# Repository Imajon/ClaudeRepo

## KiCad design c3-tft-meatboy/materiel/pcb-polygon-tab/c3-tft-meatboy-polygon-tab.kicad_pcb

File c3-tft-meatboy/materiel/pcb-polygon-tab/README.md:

# c3-tft-meatboy — PCB « MA CONSOLE » (contour = textePCB.svg), routé

Géométrie identique à `../polygon-tab-lettres.svg`. Contour 110 x ~78 mm : lettres « MA CONSOLE » en haut, corps polygone.
Généré par `../make_kicad_tab.py` (+ routeur `../route_tab.py`), Gerbers exportés avec kicad-cli.

## Câblage (= .ino / ../montage-c3-tft.svg)
| Signal | GPIO C3 | Écran J3 / bouton |
|---|---|---|
| SCLK | 4 | SCL (broche 3) |
| MOSI | 6 | SDA (4) |
| CS | 7 | CS (7) |
| DC | 5 | DC (6) |
| RST | 10 | RES (5) |
| 3V3 | 3V3 | VCC (2) + BLK (8) |
| GND | GND | GND (1) + boutons |
| GAUCHE | 2 | SW1 (bouton le plus à gauche) |
| DROITE | 1 | SW2 |
| SAUT | 3 | SW3 (12x12) |
| IO21 / IO20 | 21 / 20 | pastilles de fil à gauche |
| IO0 / IO8 | 0 / 8 | pastilles de fil à droite |
GPIO9 (BOOT) et 5V ne sont pas utilisés.

## État
- **Routé** : 118 segments, 16 vias, 2 couches. **DRC : 0 violation, 0 non connecté** (`drc.rpt`).
- Cuivre des lettres (blanc du SVG) à 0,35 mm du bord ; règle cuivre/bord du projet = 0,25 mm (JLCPCB min 0,2).
- QR code cuivre 14 mm → https://brique.tierslieulecercle.fr.

## À vérifier avant de commander
- Le SuperMini est posé au dos, **vu de devant sa rangée GPIO0…5V est à DROITE** (x=64,12), USB-C vers le bas. Vérifie sur ta carte réelle : pastilles 2,4 x 1,3 mm, entraxe des rangées 15,24 mm.
- Boutons 6x6 / 12x12 : empreintes simplifiées (pastilles Ø1,8 / Ø2,2) ; pattes d'un même côté reliées dans le bouton.
- Le routeur est maison (grille 0,2 mm) : relire le tracé dans KiCad avant fabrication.

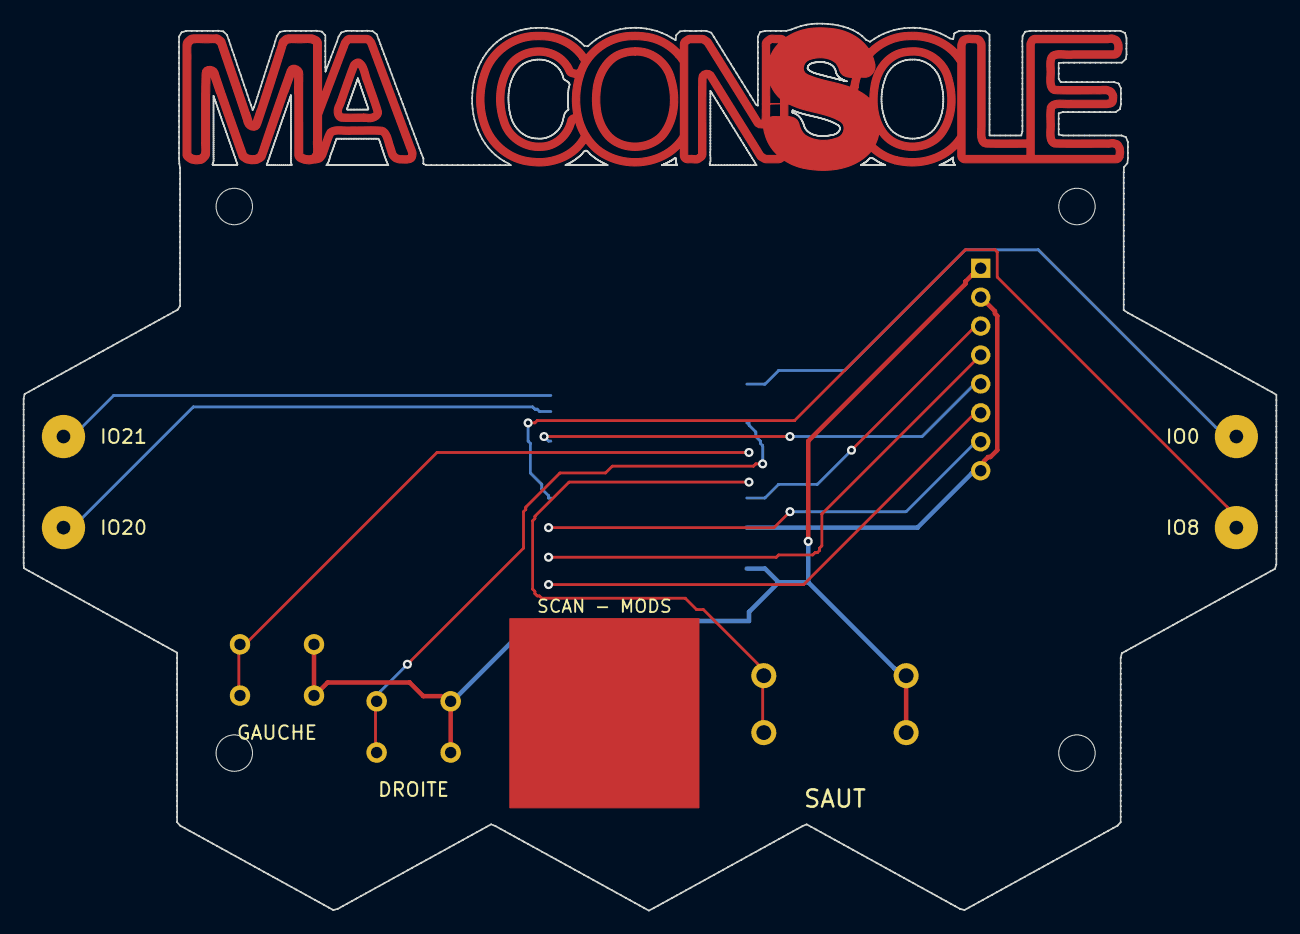
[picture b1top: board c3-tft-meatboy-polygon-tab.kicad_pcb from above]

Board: 2 copper layers, 110.0 x 77.9 mm, 13 parts (1 on the bottom side), 14 nets.

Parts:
J3: TFT_2.0in_header_1x08
MTG1, MTG2, MTG3, MTG4: MountingHole_3.2mm_M3
P1, P2, P3, P4: WirePad_3.8mm
SW1, SW2: SW_6x6
SW3: SW_12x12
U1: ESP32-C3_SuperMini_SMD

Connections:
+3V3: J3.2, J3.8, U1.6
CS: J3.7, U1.14
DC: J3.6, U1.16
DROITE: SW2.1, SW2.2, U1.2
GAUCHE: SW1.1, SW1.2, U1.3
GND: J3.1, SW1.3, SW1.4, SW2.3, SW2.4, SW3.3, SW3.4, U1.7
IO0: P3.1, U1.1
IO8: P4.1, U1.13
IO20: P2.1, U1.10
IO21: P1.1, U1.9
MOSI: J3.4, U1.15
RST: J3.5, U1.11
SAUT: SW3.1, SW3.2, U1.4
SCLK: J3.3, U1.5

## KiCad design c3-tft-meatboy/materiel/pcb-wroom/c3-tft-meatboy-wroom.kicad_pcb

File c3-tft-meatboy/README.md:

# Brique — la console de jeu que les enfants soudent eux-mêmes

**Brique** est une petite console de jeu portable à base d'**ESP32-C3** et d'un **écran TFT 2"**, conçue pour des ateliers avec des enfants (CM1 → 4ᵉ). Chaque enfant monte et soude sa propre console, puis joue à **Pixel Run**, un jeu de plateforme écrit pour la console.

Prochaine étape : laisser les enfants **créer leurs propres niveaux et règles avec une IA**, depuis un navigateur, sans rien installer.

---

## Le concept

Trois composants, trois boutons, un fer à souder. L'objectif : un objet simple à assembler, mais qui donne un vrai jeu fluide une fois allumé.

## Le matériel

| Composant | Rôle |
|---|---|
| ESP32-C3 Super Mini | Microcontrôleur Wi-Fi / ESP-NOW, USB-C |
| Écran TFT 2" ST7789 (SPI, 320×240) | Affichage |
| 3 boutons-poussoirs | Gauche (GPIO2), Droite (GPIO1), Saut (GPIO3) |
| Plaque à pastilles ou PCB hexagonal | Support |

## L'atelier

Les enfants partent des composants en vrac et repartent avec une console qui marche.

## Version 1 — prototype sur plaque à pastilles

Câblage fil à fil au dos, écran et boutons en façade.

## Version 2 — PCB hexagonal

Un PCB dédié en forme de briques hexagonales : moins de fils, montage plus rapide en atelier.

Fichiers KiCad et SVG du boîtier : [`materiel/`](materiel/).

## Le jeu : Pixel Run

- **100 niveaux** variés (ressorts, pics, blocs tombants, ennemis, scies…), étoiles à collecter, drapeau final.
- **Mode 2 joueurs** sans fil (ESP-NOW) : course avec le fantôme de l'adversaire.
- **Mini-jeux** bonus toutes les 10 étapes : Pong, Casse-brique, Invaders.
- **Quiz CM2** (maths, français, anglais) entre les niveaux, avec récompenses visuelles.
- **Classement partagé** entre consoles, boutique de skins, mascotte animée.
- Progression sauvegardée en mémoire flash.

## Compiler et flasher

Sketch Arduino : [`c3-tft-meatboy.ino`](c3-tft-meatboy.ino) (carte ESP32C3 Dev Module).

```bat
compiler-upload-c3-tft-meatboy.bat
```

Détails techniques et historique des versions : [`CONTEXTE.md`](CONTEXTE.md).

## La suite : créer son jeu avec l'IA

Idée : un firmware fixe (moteur, affichage, sons) et une IA qui génère uniquement **les niveaux et les règles** sous forme de données, envoyées à la console en quelques millisecondes depuis une page web. Le but n'est pas d'apprendre la syntaxe, mais de montrer aux enfants qu'ils peuvent **décrire, tester et corriger** un jeu qu'ils ont imaginé.

---

*AntiFaktory — 2026*

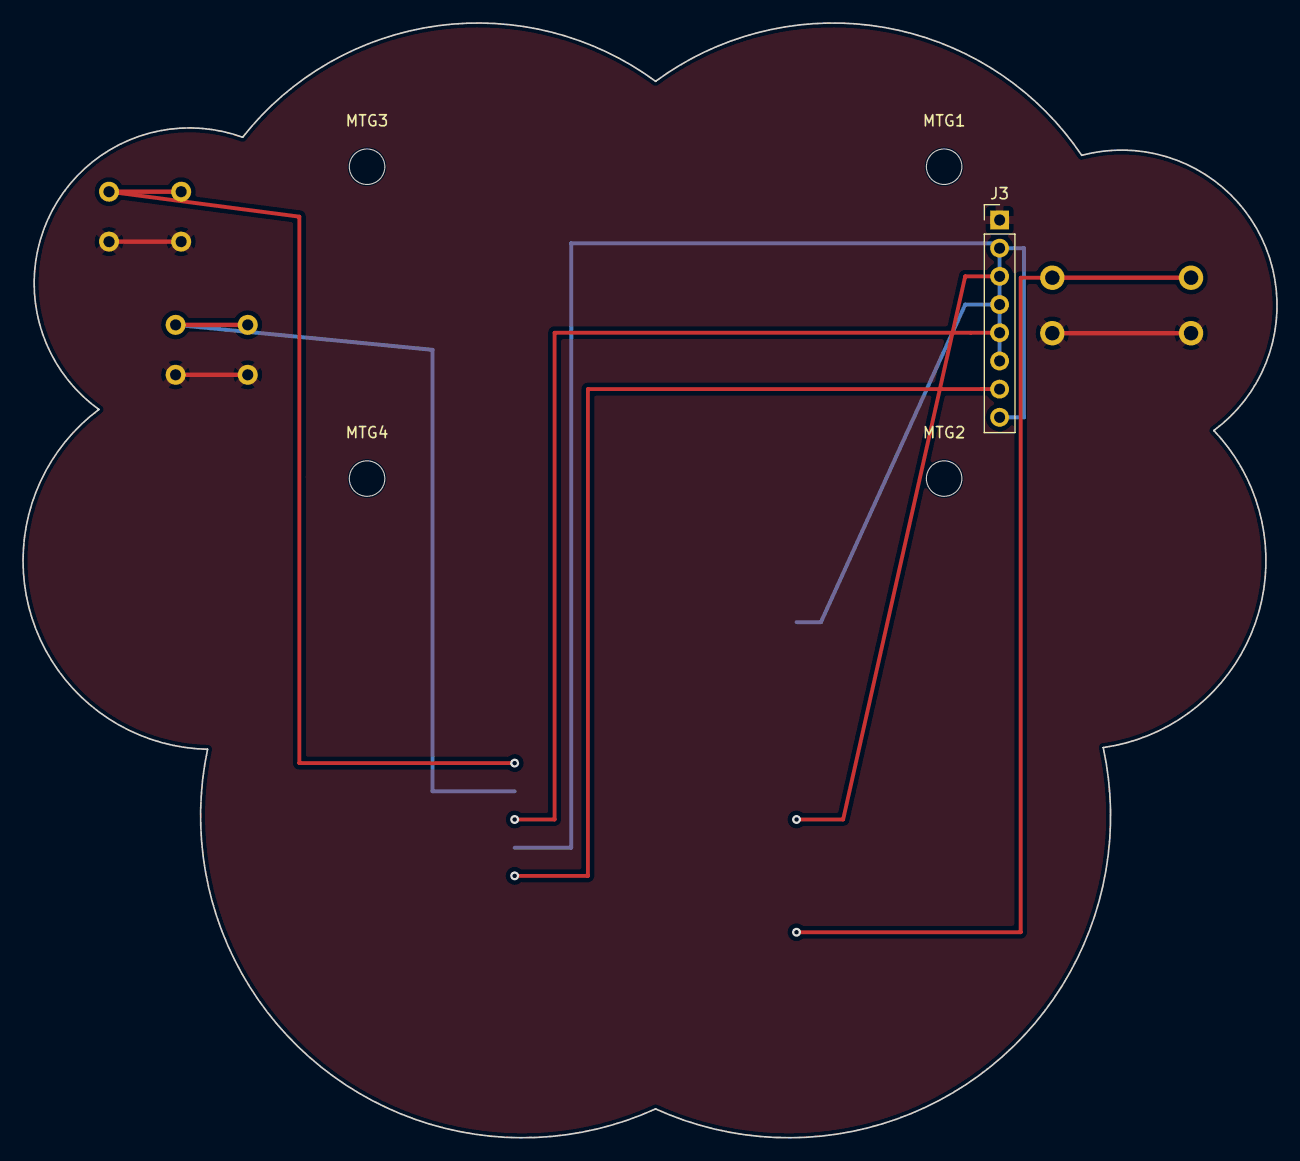
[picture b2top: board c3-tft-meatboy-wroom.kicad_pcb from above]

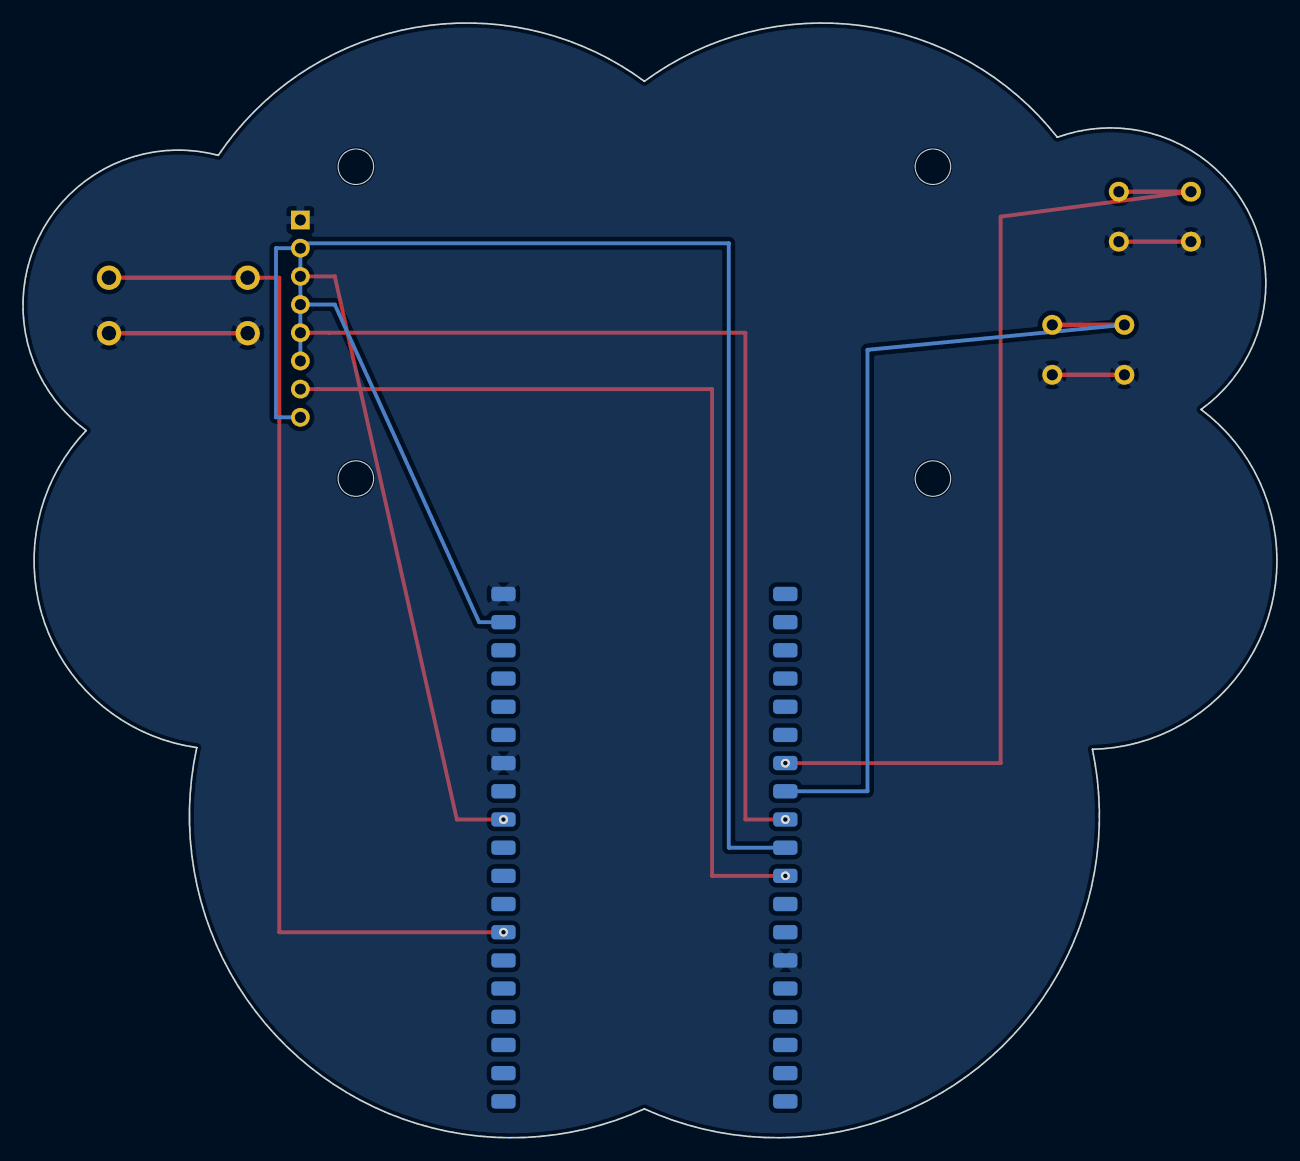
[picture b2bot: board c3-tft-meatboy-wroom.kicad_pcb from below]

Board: 2 copper layers, 113.0 x 100.4 mm, 10 parts (2 on the bottom side), 10 nets.

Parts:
J1, J2: (no value)
J3: PinHeader_1x08_P2.54mm_Vertical
MTG1, MTG2, MTG3, MTG4: MountingHole_3.2mm_M3
SW1, SW2, SW3: (no value)

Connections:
+3V3: J1.1, J3.2, J3.8
GND: J1.14, J2.1, J2.7, J3.1, SW1.2, SW2.2, SW3.2
GPIO4_SAUT: J2.13, SW3.1
GPIO18_SCLK: J2.9, J3.3
GPIO23_MOSI: J2.2, J3.4
GPIO25_RST: J1.9, J3.5
GPIO26_DC: J1.10, J3.6
GPIO27_CS: J1.11, J3.7
GPIO32_DROITE: J1.7, SW2.1
GPIO33_GAUCHE: J1.8, SW1.1

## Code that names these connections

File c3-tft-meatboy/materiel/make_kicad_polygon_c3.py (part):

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PCB = f"{D}/{NAME}.kicad_pcb"
KICAD_CLI = r"C:\Users\info\AppData\Local\Programs\KiCad\10.0\bin\kicad-cli.exe"
uid = lambda: str(uuid.uuid4())
RENAME = {"GPIO32_DROITE": "DROITE", "GPIO33_GAUCHE": "GAUCHE", "GPIO4_SAUT": "SAUT", "GPIO18_SCLK": "SCLK",
          "GPIO23_MOSI": "MOSI", "GPIO25_RST": "RST", "GPIO26_DC": "DC", "GPIO27_CS": "CS"}

s = open(SRC, encoding="utf-8").read()
for a, b in RENAME.items():
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                         shape="circle" if shape == "circle" else "rect", tht=kind == "thru_hole", front='"F.Cu"' in p))

# ---------- ESP32-C3 SuperMini au dos (identique a make_kicad_tab.py) ----------
J1 = [None, "DROITE", "GAUCHE", "SAUT", "SCLK", "+3V3", "GND", None]      # GPIO0,1,2,3,4,3V3,GND,5V
J2 = [None, None, "RST", None, None, "CS", "MOSI", "DC"]                  # GPIO21,20,10,9,8,7,6,5
if V:                                                                     # pastilles de fil du dessin ajoure
    J1[0], J2[0], J2[1], J2[4] = "IO0", "IO21", "IO20", "IO8"
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
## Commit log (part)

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2026-06-11 Lidar V1
2026-06-11 EspNowV1
2026-06-11 SentinelV2
2026-06-11 Remove node_modules from tracking
2026-06-21 Echec enfant
2026-06-21 Echec enfant V2
2026-06-21 Echec enfant V3
